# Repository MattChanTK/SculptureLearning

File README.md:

SculptureLearning
=================

<b>InteractiveSystem</b>: code for the Teensy-based system to communicate with the computer

<b>CuriousSystem2</b>: code for Curiosity Based Learning Algorithm simulation

<b>The rest</b>: old projects

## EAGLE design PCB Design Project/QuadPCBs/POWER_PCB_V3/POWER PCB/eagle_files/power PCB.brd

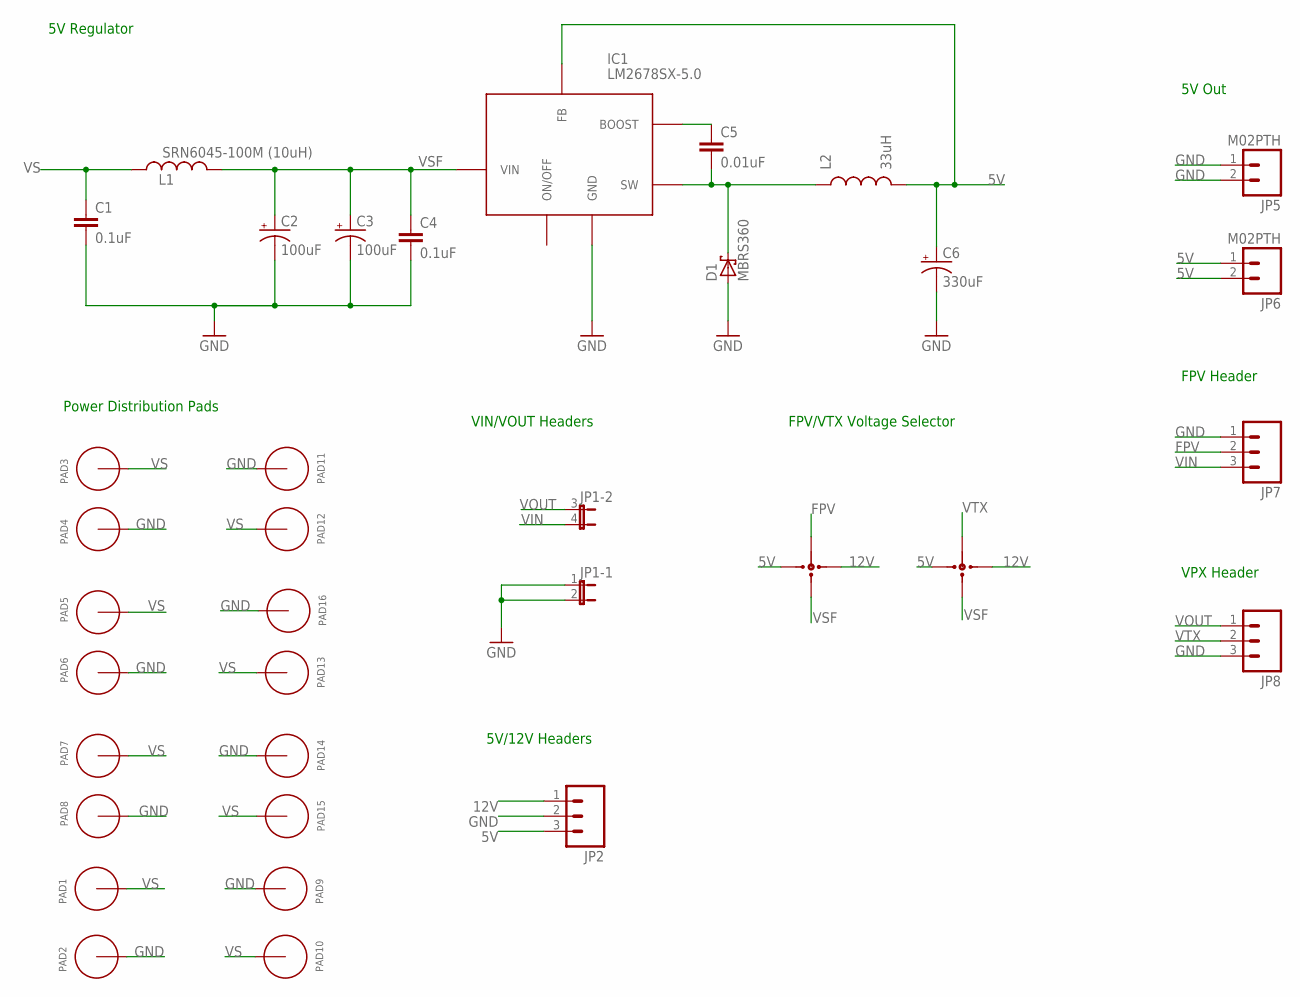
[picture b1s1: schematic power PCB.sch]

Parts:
C1, C4: 0.1uF; 0603-CAP
C2, C3: 100uF; EIA7343
C5: 0.01uF; 0603-CAP
C6: 330uF; EIA7343
D1: MBRS360; SMB
IC1: LM2678SX-5.0; P-TO263-7-1
JP1: JP2QE; JP2Q
JP2, JP7, JP8: M03PTH; 1X03
JP3, JP4: 3WAY_SMD_JUMPER; 3WAY_JUMPER
JP5, JP6: M02PTH; 1X02
L1: SRN6045-100M (10uH); SRN6045
L2: 33uH; SRN6045
PAD1, PAD2, PAD3, PAD4, PAD5, PAD6, PAD7, PAD8, PAD9, PAD10, PAD11, PAD12, PAD13, PAD14, PAD15, PAD16: PAD_3MM

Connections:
5V: C6.A (+), IC1.6 (FB), JP2.3, JP3.1, JP4.3, JP6.1, JP6.2, L2.2
12V: JP2.1, JP3.3, JP4.1
FPV: JP3.4, JP7.2
GND: C1.2, C2.C (-), C3.C (-), C4.2, C6.C (-), D1.A, IC1.4 (GND), IC1.TH (GND), JP1.1, JP1.2, JP2.2, JP5.1, JP5.2, JP7.1, JP8.3, PAD2.P$1, PAD2.P$2, PAD2.P$3, PAD2.P$4, PAD2.P$5, PAD2.P$6, PAD2.P$7, PAD2.P$8, PAD2.P$9, PAD4.P$1, PAD4.P$2, PAD4.P$3, PAD4.P$4, PAD4.P$5, PAD4.P$6, PAD4.P$7, PAD4.P$8, PAD4.P$9, PAD6.P$1, PAD6.P$2, PAD6.P$3, PAD6.P$4, PAD6.P$5, PAD6.P$6, PAD6.P$7, PAD6.P$8, PAD6.P$9, PAD8.P$1, PAD8.P$2, PAD8.P$3, PAD8.P$4, PAD8.P$5, PAD8.P$6, PAD8.P$7, PAD8.P$8, PAD8.P$9, PAD9.P$1, PAD9.P$2, PAD9.P$3, PAD9.P$4, PAD9.P$5, PAD9.P$6, PAD9.P$7, PAD9.P$8, PAD9.P$9, PAD11.P$1, PAD11.P$2, PAD11.P$3, PAD11.P$4, PAD11.P$5, PAD11.P$6, PAD11.P$7, PAD11.P$8, PAD11.P$9, PAD14.P$1, PAD14.P$2, PAD14.P$3, PAD14.P$4, PAD14.P$5, PAD14.P$6, PAD14.P$7, PAD14.P$8, PAD14.P$9, PAD16.P$1, PAD16.P$2, PAD16.P$3, PAD16.P$4, PAD16.P$5, PAD16.P$6, PAD16.P$7, PAD16.P$8, PAD16.P$9
unnamed: C5.1, IC1.3 (BOOST)
unnamed: C5.2, D1.C, IC1.1 (SW), L2.1
VIN: JP1.4 (2), JP7.3
VOUT: JP1.3 (1), JP8.1
VS: C1.1, L1.1, PAD1.P$1, PAD1.P$2, PAD1.P$3, PAD1.P$4, PAD1.P$5, PAD1.P$6, PAD1.P$7, PAD1.P$8, PAD1.P$9, PAD3.P$1, PAD3.P$2, PAD3.P$3, PAD3.P$4, PAD3.P$5, PAD3.P$6, PAD3.P$7, PAD3.P$8, PAD3.P$9, PAD5.P$1, PAD5.P$2, PAD5.P$3, PAD5.P$4, PAD5.P$5, PAD5.P$6, PAD5.P$7, PAD5.P$8, PAD5.P$9, PAD7.P$1, PAD7.P$2, PAD7.P$3, PAD7.P$4, PAD7.P$5, PAD7.P$6, PAD7.P$7, PAD7.P$8, PAD7.P$9, PAD10.P$1, PAD10.P$2, PAD10.P$3, PAD10.P$4, PAD10.P$5, PAD10.P$6, PAD10.P$7, PAD10.P$8, PAD10.P$9, PAD12.P$1, PAD12.P$2, PAD12.P$3, PAD12.P$4, PAD12.P$5, PAD12.P$6, PAD12.P$7, PAD12.P$8, PAD12.P$9, PAD13.P$1, PAD13.P$2, PAD13.P$3, PAD13.P$4, PAD13.P$5, PAD13.P$6, PAD13.P$7, PAD13.P$8, PAD13.P$9, PAD15.P$1, PAD15.P$2, PAD15.P$3, PAD15.P$4, PAD15.P$5, PAD15.P$6, PAD15.P$7, PAD15.P$8, PAD15.P$9
VSF: C2.A (+), C3.A (+), C4.1, IC1.2 (VIN), JP3.2, JP4.2, L1.2
VTX: JP4.4, JP8.2

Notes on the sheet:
Power Distribution Pads
VIN/VOUT Headers
5V/12V Headers
FPV/VTX Voltage Selector
5V Out
5V Regulator
FPV Header
VPX Header

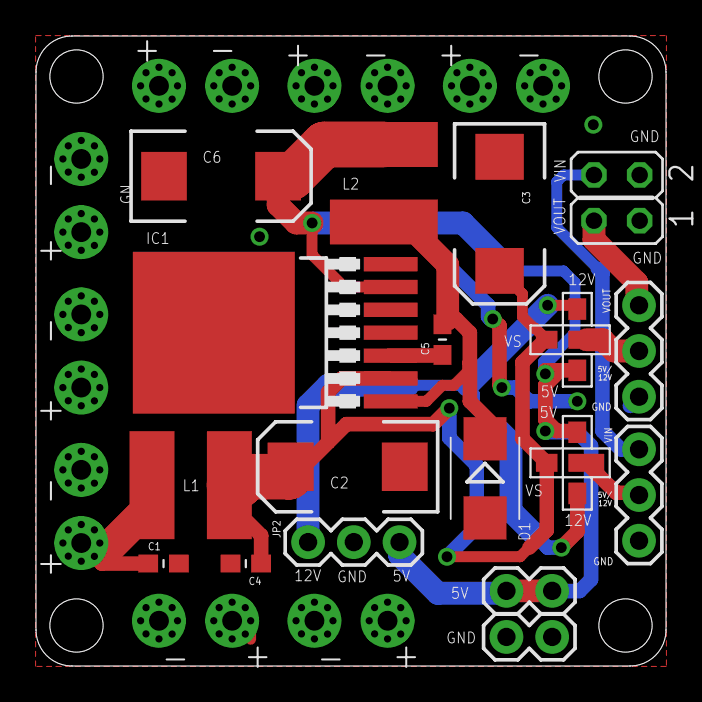
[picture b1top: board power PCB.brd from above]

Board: 2 copper layers, 35.0 x 35.0 mm, 34 parts (0 on the bottom side), 11 nets.

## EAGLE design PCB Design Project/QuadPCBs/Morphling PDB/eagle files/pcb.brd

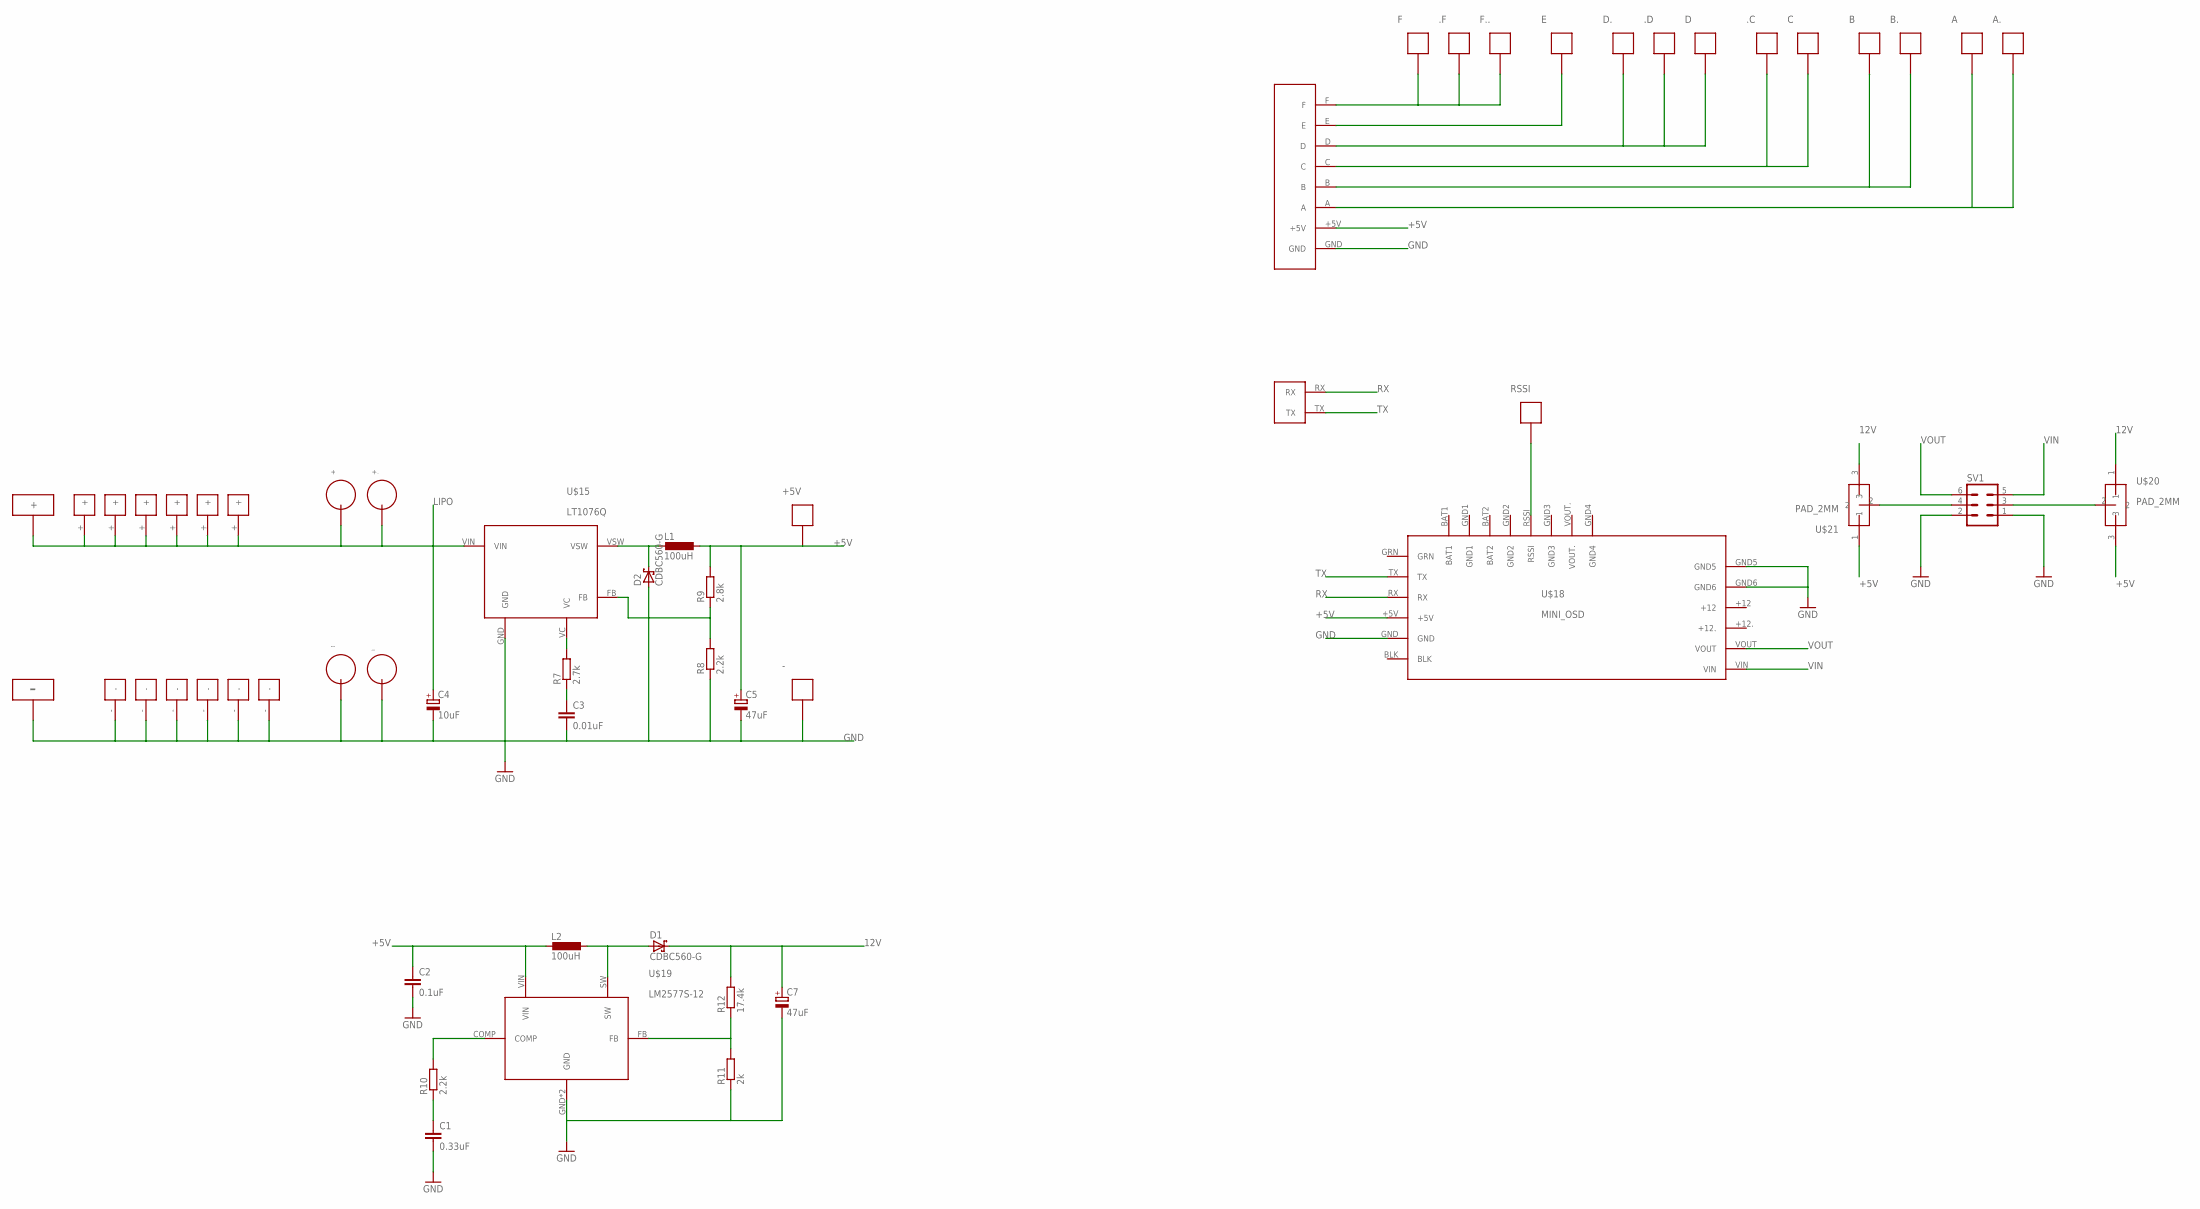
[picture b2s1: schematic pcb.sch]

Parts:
+, +.: PAD_POWER
+5V: PAD3-A
-: PAD3-A
--: PAD_POWER
.C, .D, .F: PAD3-A
A, A.: PAD3-A
B, B.: PAD3-A
C: PAD3-A
C1: 0.33uF; C1206
C2: 0.1uF; C1206
C3: 0.01uF; C1206
C4: 10uF; 153CLV-0505
C5, C7: 47uF; 153CLV-0505
D, D.: PAD3-A
D1, D2: CDBC560-G; SMC
E: PAD3-A
F, F..: PAD3-A
L1, L2: 100uH; DO3316P
R7: 2.7k; R0805
R8, R10: 2.2k; R0805
R9: 2.8k; R0805
R11: 2k; R0805
R12: 17.4k; R0805
RSSI: PAD3-A
SV1: MA03-2
U$1: PAD6X3.5-; PAD6X3.5
U$2: PAD6X3.5+; PAD6X3.5
U$3, U$4, U$7, U$8, U$13, U$14: PAD3.81+; PAD3.81
U$5, U$9, U$10, U$11, U$12, U$22: PAD3.81-
U$15: LT1076Q; LT1076
U$16: 2.54HEADER8
U$17: 2.54HEADER
U$18: MINI_OSD
U$19: LM2577S-12; TO-263
U$20, U$21: PAD_2MM
_: PAD_POWER

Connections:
12V: C7.+, D1.C, R12.2, U$20.1, U$21.3
+5V: +5V.1, C2.1, C5.+, L1.2, L2.1, R9.2, U$16.+5V, U$18.+5V, U$19.VIN, U$20.3, U$21.1
GND: -.1, --.P$1, --.P$2, --.P$3, --.P$4, --.P$5, --.P$6, --.P$7, --.P$8, --.P$9, C1.2, C2.2, C3.2, C4.-, C5.-, C7.-, D2.A, R8.1, R11.1, SV1.1, SV1.2, U$1.P$1, U$5.-, U$9.-, U$10.-, U$11.-, U$12.-, U$15.GND, U$16.GND, U$18.GND, U$18.GND5, U$18.GND6, U$19.GND, U$19.GND1 (GND), U$22.-, _.P$1, _.P$2, _.P$3, _.P$4, _.P$5, _.P$6, _.P$7, _.P$8, _.P$9
LIPO: +.P$1, +.P$2, +.P$3, +.P$4, +.P$5, +.P$6, +.P$7, +.P$8, +.P$9, +..P$1, +..P$2, +..P$3, +..P$4, +..P$5, +..P$6, +..P$7, +..P$8, +..P$9, C4.+, U$2.P$1, U$3.+, U$4.+, U$7.+, U$8.+, U$13.+, U$14.+, U$15.VIN
unnamed: RSSI.1, U$18.RSSI
unnamed: R10.2, U$19.COMP
unnamed: .F.1, F.1, F...1, U$16.F
unnamed: C3.1, R7.1
unnamed: D2.C, L1.1, U$15.VSW
unnamed: R11.2, R12.1, U$19.FB
unnamed: SV1.4, U$21.2
unnamed: R8.2, R9.1, U$15.FB
unnamed: R7.2, U$15.VC
unnamed: E.1, U$16.E
unnamed: SV1.3, U$20.2
unnamed: .D.1, D.1, D..1, U$16.D
unnamed: .C.1, C.1, U$16.C
unnamed: B.1, B..1, U$16.B
unnamed: C1.1, R10.1
unnamed: A.1, A..1, U$16.A
unnamed: D1.A, L2.2, U$19.SW
RX: U$17.RX, U$18.RX
TX: U$17.TX, U$18.TX
VIN: SV1.5, U$18.VIN
VOUT: SV1.6, U$18.VOUT

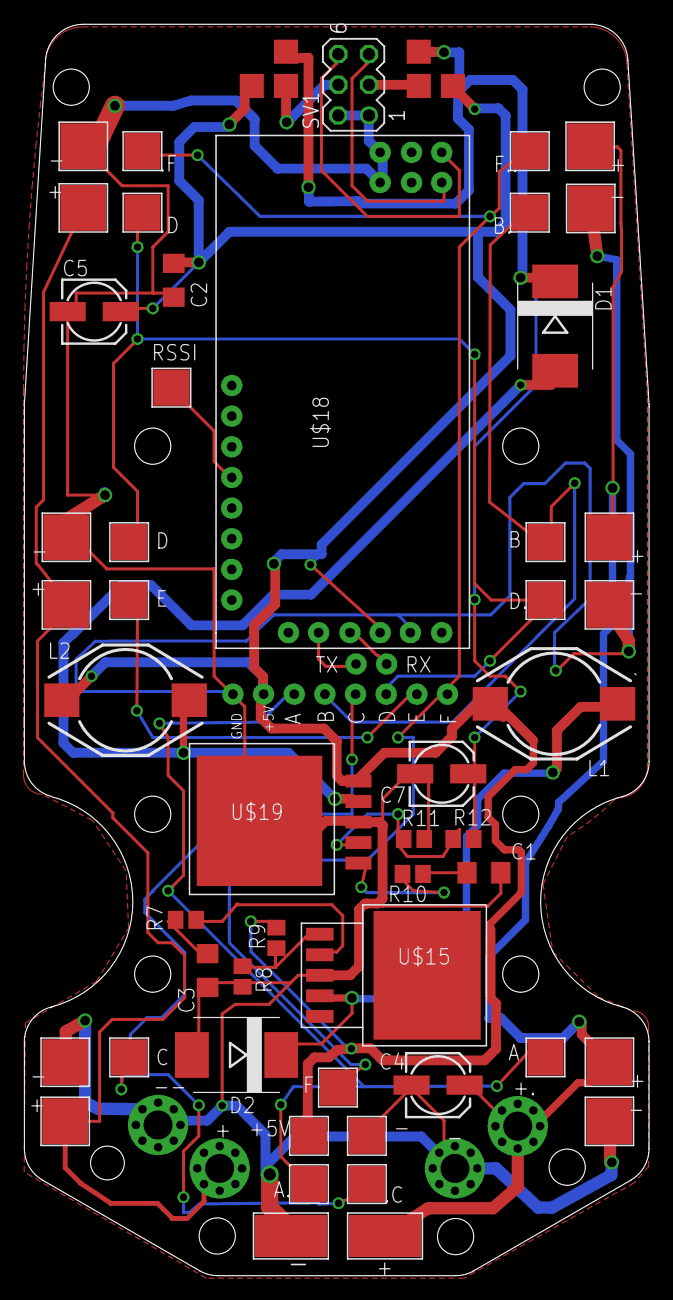
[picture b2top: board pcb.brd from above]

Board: 2 copper layers, 51.8 x 103.7 mm, 58 parts (0 on the bottom side), 25 nets.

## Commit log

2013-11-06 First real commit
2013-11-06 Changed SimSon speed
2013-11-07 Speed is now scaled by distance to attrractor.
    Maybe want to do it differently.
2013-12-11 Added Tentacle simulation
    also some small changes made long time ago on simulated audience
2013-12-12 Fixed the bug about extending beyond max length Added Tentacle object
2013-12-12 Simple code to test if the Tentacle actually go to where if supposes to given num of SMA activation as input
2013-12-12 Add PID controller Plotted results
2013-12-12 Tested on sine curve reduced the warming and cooling rate.
2013-12-14 Changed folder name to add the word "Simulation"
2013-12-14 Added Arduino code for the Tentacle that uses Segemented Binary Control
2013-12-14 Added code that implement duty cycle
2013-12-15 Completed manual control mode
2013-12-15 Not able to measure rotation
2013-12-16 got the Tentacle controller working on Arduino
    Started on a readSerial python code to take the error data out
2013-12-16 able to read time
2013-12-17 Python code that used to read serial data and save it as csv file
2013-12-19 Modified for different tests
2014-02-11 Added EmoGame with Panda 3D
    also moved some codes to the back-up folder
2014-02-11 Ball game
2014-02-11 simple hit the ball game
2014-02-12 2D bouncing ball working
2014-02-12 added the hand
2014-02-13 added many spirits
2014-02-13 Adding the pictures
2014-02-13 changed the angel behaviours
2014-02-13 added walk2 is has more generic motion equation
2014-02-13 Now the balls bounce back at the right angles!
2014-02-14 better behaviour and consistant speed
2014-03-16 remove the interaction capability by taking "Candy" out form instantiation.
2014-03-20 Copying the EmoGame to make new software for the study
2014-03-20 Compiled. Added motor, etc.
2014-03-20 compiled set up the basic structure of the robot.
2014-03-20 Compiled (working on new data structure for memory)
2014-03-20 updateRegion Code
2014-03-20 check that it does split the region when over C1, but only once
2014-03-20 Splitting more than once
2014-03-21 compiled with region splitting!
2014-03-21 splitting with previous cut values
2014-03-22 Added codes to forget exemplars and region! All a test code for doing some simple tests
2014-03-22 fix the bug about wrong dimension
2014-03-22 Added learning progress calculation method
2014-03-23 Implemented Expert
2014-03-23 fixed the bug about having the same values for every component
2014-03-23 added learning progress calculation
2014-03-24 Added and tested discretizer
2014-03-24 Added dictionary to store q value
2014-03-24 completed all basic requirements for the CDLA
2014-03-24 Added way to output to csv
2014-03-24 graphing code
2014-03-24 updated with percent action and other stuffs
2014-04-09 Solved the lag problem when splitting region by eleiminating the multiple vj guesses
2014-04-10 changed velocity control to acceleration control; fixed bug about orientation (pygame y goes downward.)
2014-04-10 new SimSon response model (not sure if it's working)
2014-04-10 adding coupling of two robots
2014-04-10 implemented key board slider
2014-04-11 Add the Q_learning code and Arduino code
2014-04-11 Calibrating for 2s so that the heart beat properly captured.
2014-04-15 Ardunio new way to o heart rate
2014-04-15 tried to add way to smooth out hr
2014-04-15 Conflict?
2014-04-15 Rollback
2014-04-16 Interfaced with sensors using thread
2014-04-17 output only data of one robot. fixed bug on closing port before finished reading. Fixed problem with start learning before sensor data is coming.
2014-04-17 added ways to turn on and data collection and simulation working on the problem of dots slowing down over time
2014-04-20 Changed some modelling and sync parameters.
2014-04-22 Added ways to plot sensor input graph
2014-04-24 adding ways to have simple simulation mode
2014-04-24 Implemented simpleMode
2014-04-24 export function modified
2014-04-24 added some more graphing capabilities
2014-04-25 added more graphs and the mode that takes in internal states
2014-04-25 minor updates
    Changed simulated sensor input (non-simple mode)
2014-06-30 Added way to plot graphs automatically
2014-06-30 Time series output added
2014-06-30 state-space diagram added
2014-07-01 variance calculation divide by mean learn progress calculation divide by mean
2014-07-02 Modified for demo
2014-07-07 First check in for new CBLA codes.
2014-07-07 Added algorithm steps in comments
2014-07-07 Added the SimSystem with basic structure
2014-07-08 ad hoc q-learning algorithm with random placeholders
2014-07-08 q-learning with action selection kind of working
2014-07-08 fix some bugs from the previous commit
2014-07-08 save before moving to version without using tile coding
2014-07-08 simplest q-learning working (seem to) bound to (0,1)
2014-07-08 Working CuriousSystem, start on the main()
2014-07-08 added q-learner to main()
2014-07-08 q-learning tested added dict for expert exemplars
2014-07-08 fix the tuple problem with add_to_training_set
2014-07-09 added 3D plot of model!
2014-07-09 added K-mean clustering but just using model[0] (i.e. 1 cluster) for now
2014-07-09 Change simulation to a sin curve and svr to linear plotted 3D graph; seems to work
2014-07-10 changed to cos and wider curve change dict to setl this allow duplicate in exemplar's values
2014-07-10 Fixed the bug which state0 and action0 were swapped!
2014-07-15 new program that save figure automatically to png
2014-07-15 Setting up the Teensy as an USB HID device
2014-07-15 Added flashing led and an attempt to read message
2014-07-15 Got rawhid.py sending and receiving!
2014-07-16 got pyusb to send and receive!!!
2014-07-16 decoded message echoed from Teensy
2014-07-16 working updated code.
2014-07-16 updated Teensy working code
2014-07-17 Modularized and listen and respond version of pyUSB_test
2014-07-17 Modularized and listen and respond version of the Teensy code
2014-07-17 fully Modularized and listen and respond version of the PyUSB code
2014-07-17 with read time print-out
2014-07-21 64 bytes with 990us echo
2014-07-21 added multi threading
2014-07-21 multi-thread with queue
2014-07-21 added code that is used to change priority
2014-07-23 don't actually need parititon fixed some bugs
2014-07-24 Copied to a new directory for interactive behaviours tests
2014-07-24 added ways to pack and unpack intergers
2014-07-24 Go to change the blinking frequency of several Teensy from the computer
2014-07-24 added is to each message to allow each message to be verified
2014-07-24 fixed the blocking problem by not having the Teensy to talk to PC repeatedly
2014-07-29 added the system parameter class
    Teensy code added timeout to the send command
2014-07-30 new code able to turn on and off a specific Teensy
2014-07-30 got flashing LED working as well
2014-07-30 increased the send timeout to 50ms to allow the led blink to sychronize
2014-07-30 added exception handling when claiming the device
2014-07-30 move the reading data again within the loop so that it actually won't stuck at the invalid data part.
2014-07-30 changed the threading event and wait
2014-07-30 added an if statement so that it won't update the parameter list every loop on the arduino. Instead, only does so when there is a new message
2014-07-30 got reply with sensor reading working
2014-07-31 added wait for sensor reading
2014-07-31 move parsing messages out of the print-to-term statement
2014-07-31 added code that automatically modify the period and record echo time.
2014-07-31 added code that ensure that the sensor measurement correspond to the latest action
2014-08-01 experimented with end point type. didn't really change speed
2014-08-01 added change priority in the Teensy interface thread too modify the the changing period frequency
2014-08-01 Added interactive code that respond to analog0; tested on only one Teensy though
2014-08-02 Changed code to Python 3.3 and added a space holder for the GUI
2014-08-02 changed system parameter to dictionary based
2014-08-02 added command objects
2014-08-02 integrated interactivecmd with the main thread
2014-08-02 fixed some bugs
2014-08-02 added some debugging info
2014-08-02 modified Teensy code so that it starts off setting the timer
2014-08-04 Included sensor reading and support multiple Teensy devices fixed Teensy code's bug. It wouldn't turn on if the period doesn't change.
2014-08-04 added time measurement
2014-08-04 added inheritance; Hardcorded version inherit the interactive version
2014-08-05 able to integrate multiple Teensys
2014-08-06 Teensy code: clear all existing messages; new code based for simplified test unit Added subclasses for different configurations
2014-08-06 got the Tentacle board working and integrated.
2014-08-06 got SMA to cycle at a specific on and off pattern
2014-08-07 added sound module
2014-08-08 forgotten committs
2014-08-19 failed attempt to allow additon and removal of Teensy devices. the non-working code are commented.
2014-08-19 moved the 'All Thread Terminated' printout under the Teensy Manager and deleted all the commented non-working codes.
2014-08-19 Create gh-pages branch via GitHub
2014-08-19 Changed name of the folder
2014-08-19 added space
2014-08-19 Added gitignore file
2014-08-19 Changed some wording in the tagline
2014-10-17 moved around some files
2014-10-17 Added block diagram
2014-10-17 Angelica's Friend's PCB project
2014-10-17 added hardware igrnore extensions
2014-10-17 modified the Schematic
2014-10-17 Deleting the back-up files
2014-10-18 layout of component
    problem with input cap for the switching regulator
2014-10-19 Updated block diagrams
2014-10-21 finished PCB design
    Change regulator back to LM7689 but in TO-203-7 package

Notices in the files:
parts and their libraries:
SparkFun-Passives: Licensing: Creative Commons ShareAlike 4.0 International - https://creativecommons.org/licenses/by-sa/4.0
